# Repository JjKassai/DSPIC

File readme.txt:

Basic setup to turn on the ADC and DAC, and it just spits out the signal at the DAC with a linear multiplier.  It has about a 600us delay.

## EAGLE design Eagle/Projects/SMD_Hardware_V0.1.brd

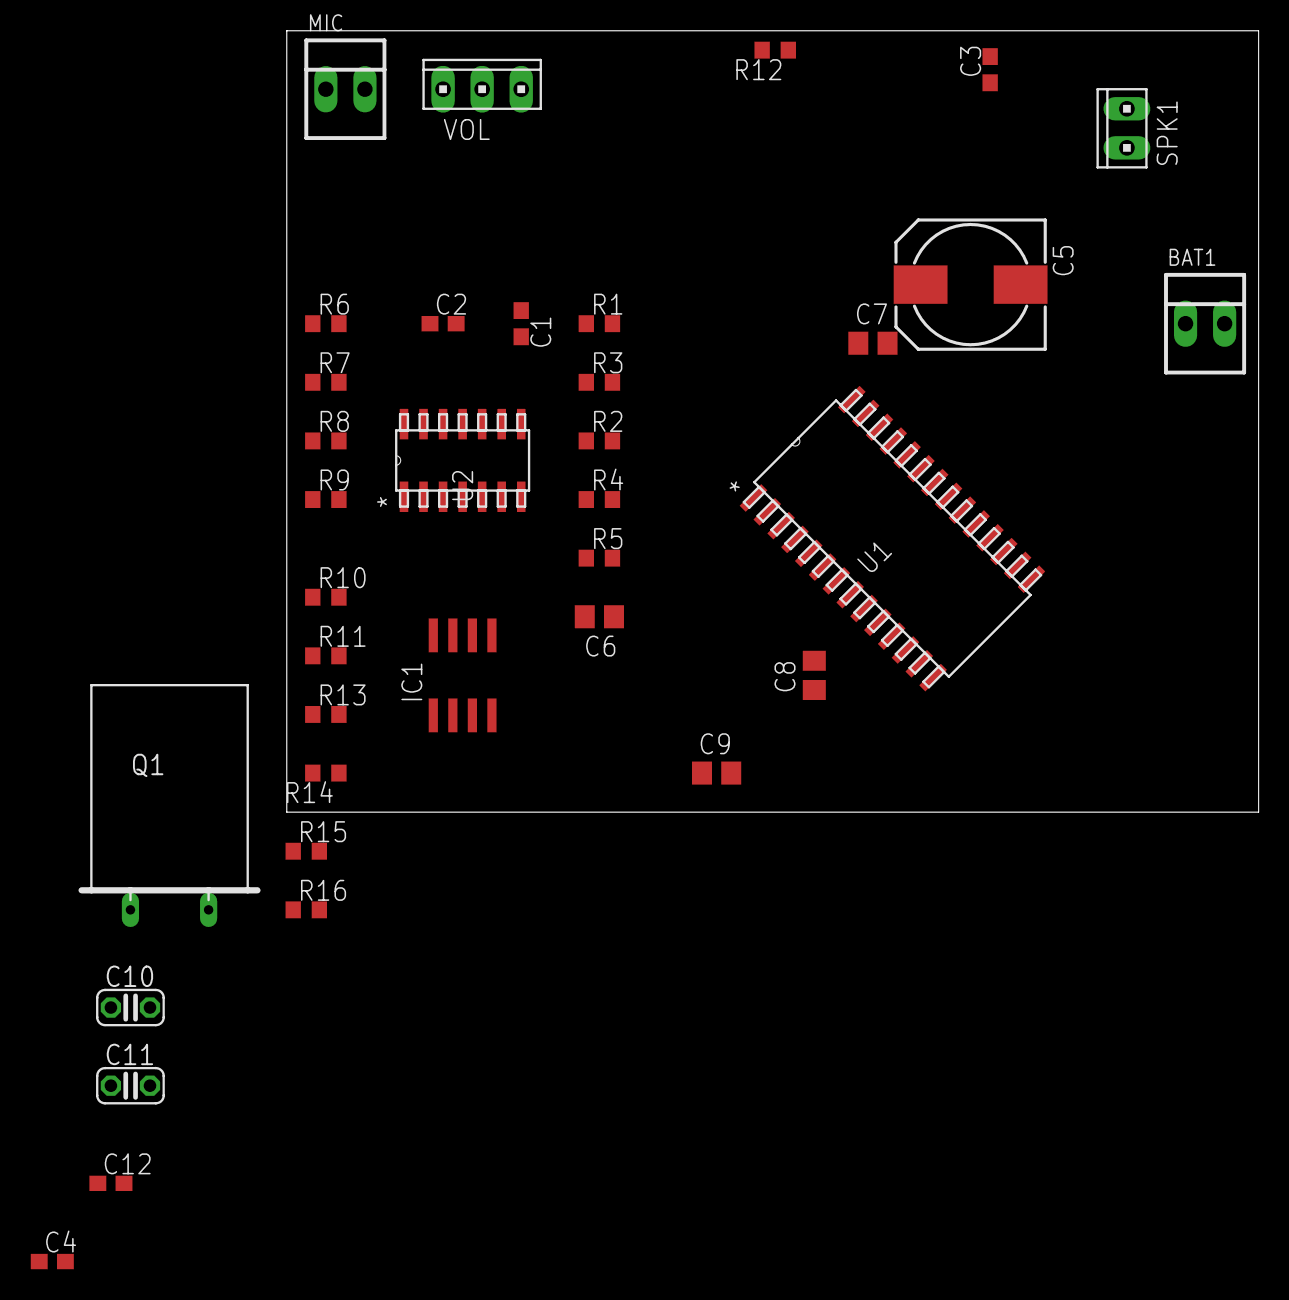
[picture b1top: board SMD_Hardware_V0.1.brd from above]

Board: 2 copper layers, 63.2 x 50.8 mm, 36 parts (0 on the bottom side), 26 nets, no tracks yet.

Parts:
BAT1: 22-23-2021
C1, C4: .1uF; C0603
C2: C0603
C3: .05uF; C0603
C5: 220uF 25V; 140CLH-0810
C6, C7, C8: C0805
C9: DNI; C0805
C10, C11: 10pF; C025-024X044
C12: 10uF; C0603
IC1: LM386M-1; SO08
MIC: 22-23-2021
Q1: 12 MHz (ATS12A); Q
R1, R4, R5, R6, R7, R8, R9, R10, R11, R13: 10k; R0603
R2, R15, R16: 1k; R0603
R3: 100k; R0603
R12: 10; R0603
R14: 0; R0603
SPK1: 10X02MTA
U1: DSPIC33FJ128GP802-X_SO; SOIC28-W_MC
U2: MCP6024-X/SL; SOIC14-N_MC
VOL: 10X03MTA

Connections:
GND: BAT1.1, C6.2, C7.1, C8.1, C9.2, C10.2, C11.2, C12.1, C12.2, IC1.2, IC1.4, MIC.2, R4.1, R11.1, R12.1, R16.1, SPK1.2, U1.8, U1.19, U1.27, U2.11, VOL.3
unnamed: C1.1, MIC.1, R1.1
unnamed: C1.2, R2.1
unnamed: R2.2, R3.1, U2.2
unnamed: R4.2, R5.1, U2.3
unnamed: R9.1, R10.1, R11.2
unnamed: C2.1, R8.1, U2.14
unnamed: R6.1, R8.2, U2.13
unnamed: R7.2, U1.24
unnamed: R7.1, R9.2, U2.12
unnamed: R6.2, U1.23
unnamed: C4.1, R15.2, R16.2, U1.2
unnamed: BAT1.2, IC1.6
unnamed: C2.2, VOL.1
unnamed: C3.2, C5.+, IC1.5
unnamed: C3.1, R12.2
unnamed: C5.-, SPK1.1
unnamed: C6.1, U1.20
unnamed: R3.2, U2.1
unnamed: C9.1, R13.1, R14.2
unnamed: R14.1, U1.1
unnamed: IC1.3, VOL.2
unnamed: C11.1, Q1.1, U1.9
unnamed: C10.1, Q1.2, U1.10
unnamed: C7.2, C8.2, U1.13, U1.28
VDD: R1.2, R5.2, R10.2, R13.2, R15.1

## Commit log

2015-05-11 Added the initial project files - code just spits out the adc onto the DAC with a linear multiplier
2015-05-11 Added the readme file
2015-05-11 Created a branch for the function generator work and added a readme file
2015-05-11 Added a readme file
2015-05-17 Updated the gain values, changed the hardware to use an op amp for the mic preamp rather than the transistor, so the gain is turned down.
2015-05-17 Added datasheets
2015-05-17 Updated the setup code to be more clear, cleaned up the comments, removed some old debug code
2015-05-17 Added the audio preamp schematic, cleaned up the code a bit. Working well with the current hardware architecture.
2015-05-22 Added some more reference information
2015-05-25 Added a matlab sscript to experiment with some ways to change the audio
2015-05-25 Added the language libaries guide that discusses the math functions
2015-05-25 Cleaned up the code a bit
2015-05-25 Added some datasheets, still working on the code. Need to determine the sample rate of the ADC
2015-05-26 Added a sampling calculator spreadsheet and some new code, as well as split the lookup tables out into their own header file
2015-05-26 Added some eagle libraries for board layout
2015-05-26 Updated some code and added some eagle starter files
2015-05-27 Started a rough board layout
2015-05-28 Cleaned up the datasheets directory and added the microphone preamp circuit
2015-05-28 Layed out the board a bit more, finished off some connections for the basic micro layout. Need to add a power supply yet
2016-08-02 Added a few documents related to the audio input preamp
2016-08-02 Renamed the datasheets folder to Datasheets&Literature
2016-08-02 Cleaning up the code, should be binary equivalent
2016-08-03 Cleaned up the code more, preparing for cleaning the whole repository
2016-08-03 Cleaned up the code, started a gitignore file
2016-08-03 Removing files that should be omitted by the gitignore file
2016-08-03 Created a Documentation folder
2016-08-03 More code clean up, added some documentation on audio processing, and added a brainstorming text file
2016-08-03 Started to create some diagnostics, still refactoring code
2016-08-04 Started editing the eagle files with values from the breadboard, and was working on the code a bit more
2016-08-04 Eagle changes
2016-08-04 Fixed up the calculators, added calculator for proper 40MIPs operation, and added the code to update the oscillator configuration
2016-08-04 Tried to calculate the correct values for DAC and ADC setup, and created an interrupt routine to test them. Calculator updated with relevant calculations
2016-08-05 More code modularization, added the Family Reference document for the TIMER module
2016-08-05 Started a source code folder for the sake of organization
2016-08-05 Added UART code, added the UART family reference guide. Created interrupt routines for the UART.
2016-08-06 Fixed errors caused by using x^y notation not supported and cleaned up the code more. Set up main function to do basic diagnostics
2016-08-06 Fixed some overflow problems, added some DAC functionality.
2016-08-06 Fixed the auxiliary clock setup to get the DAC speed up to 44kHz. Working
2016-08-06 Got the echo function working, had to change the gain
2016-08-06 Updated the schematic a bit, lowered the ADC gain to not use digital gain. Trying to improve the analog to take care of this
2016-08-10 Added some highlights to the datasheet and added some calculations. These need to be cleaned up
2016-08-11 Added some material from wikipedia on pitch shifting
2016-08-11 Updated the matlab scripts
2016-08-11 Added a matlab script I found online that does pitch shifting. Haven't tested it yet.
2016-08-12 Added a macro-enabled excel workbook to explore matching ADC and DAC sample rates
2016-11-10 Cleaned up the schematic a bit and added an app note about anti-aliasing filters for ADC (which will need to be implemented)
2016-11-11 Added a spice model of the anti-aliasing filter from the T.I. App Note
2016-11-11 Started a 2nd rev of the PCB to include a voltage regulator and anti-aliasing filter, added a Microchip filterLab file for a 20kHz 4th order Butterworth
